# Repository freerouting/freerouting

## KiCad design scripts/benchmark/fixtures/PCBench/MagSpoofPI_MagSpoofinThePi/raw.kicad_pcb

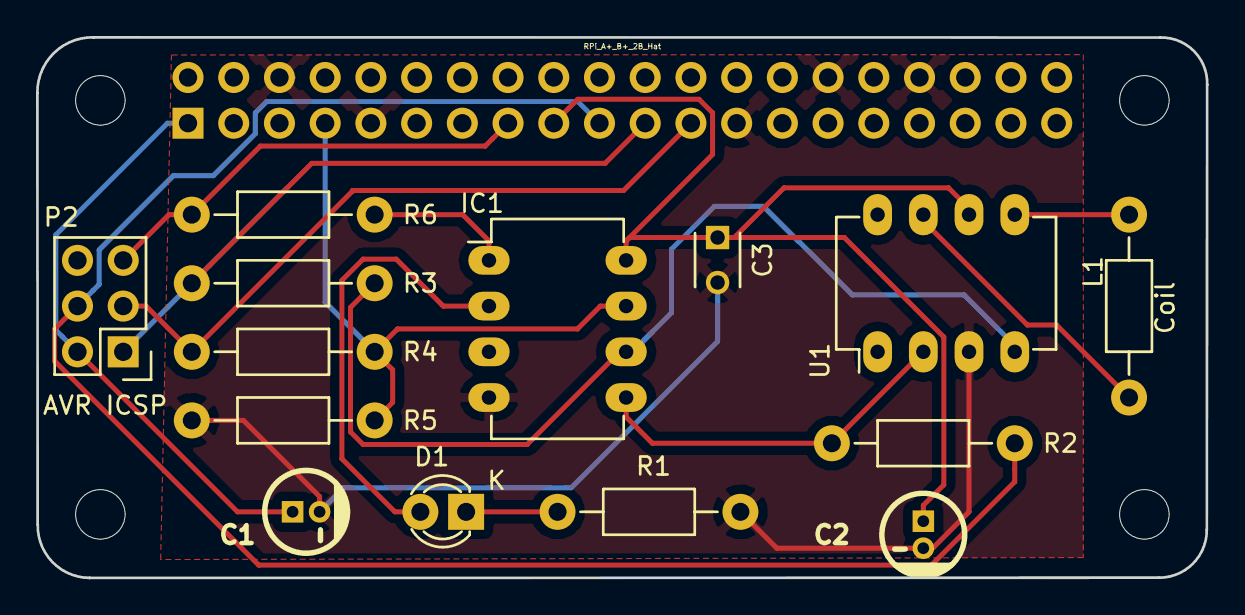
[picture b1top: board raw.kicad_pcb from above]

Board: 2 copper layers, 65.0 x 30.0 mm, 15 parts (0 on the bottom side), 14 nets.

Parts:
C1, C2: 100uF; CP_4x5mm
C3: 0.1uF; C_Disc_D3_P2.5
D1: LED; LED-3MM
IC1: ATTINY85-P; DIP-8_W7.62mm_LongPads
L1: Coil; Resistor_Horizontal_RM10mm
P2: AVR ICSP; Pin_Header_Straight_2x03
R1: 330; Resistor_Horizontal_RM10mm
R2, R3, R4, R6: 1K; Resistor_Horizontal_RM10mm
R5: 10K; Resistor_Horizontal_RM10mm
U1: TC4424; DIP-8_W7.62mm_LongPads
U2: RPi_A+_B+_2B_Hat; z_RPiZero_Hat_NPTH

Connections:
/GPIO4: IC1.7, R4.2, R5.1, U2.7
/MISO: P2.1, R3.1, U2.21
/MOSI: P2.4, R2.1, U2.19
/RST: P2.5, R6.2, U2.15
/SCK: P2.3, R4.1, U2.23
GND: C1.2, C2.2, C3.2, IC1.4, P2.6, R1.2, R5.2, U1.3, U2.6, U2.9, U2.25, U2.30, U2.34
unnamed: D1.1, R1.1
unnamed: D1.2, IC1.2
unnamed: IC1.1, R6.1
unnamed: IC1.5, R2.2, U1.2
unnamed: IC1.6, R3.2, U1.4
unnamed: L1.1, U1.7
unnamed: L1.2, U1.5
VCC: C1.1, C2.1, C3.1, IC1.8, P2.2, U1.6, U2.1, U2.17

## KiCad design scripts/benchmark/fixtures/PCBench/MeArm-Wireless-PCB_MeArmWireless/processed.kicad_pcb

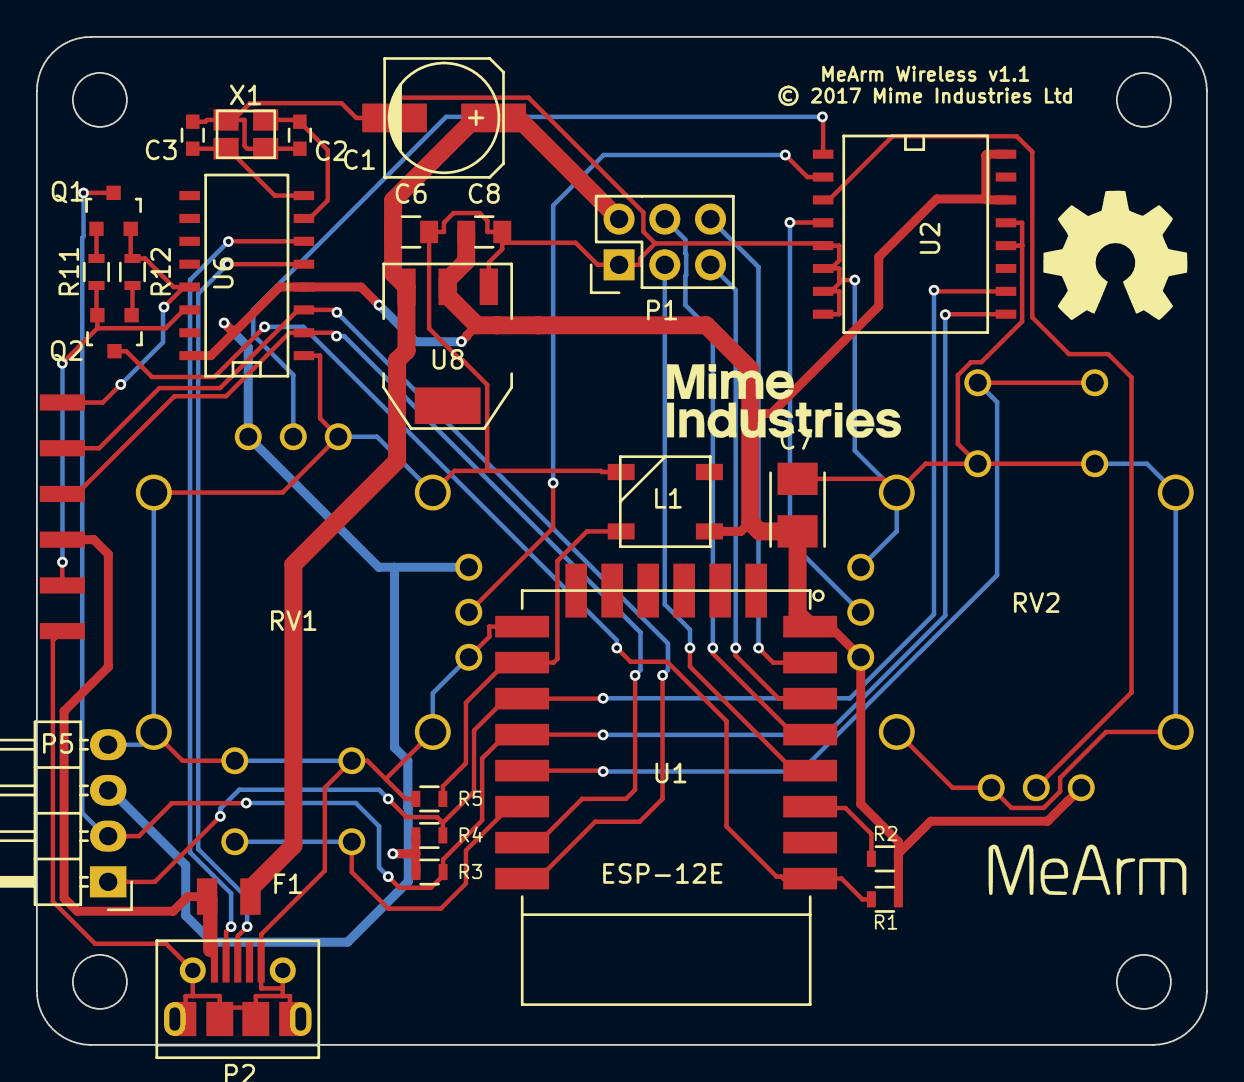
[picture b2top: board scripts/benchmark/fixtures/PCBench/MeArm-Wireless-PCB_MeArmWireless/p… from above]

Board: 2 copper layers, 65.0 x 56.0 mm, 31 parts (0 on the bottom side), 29 nets.

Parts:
ART1: OSHW-LOGO; OSHW_LOGO
ART2: LOGO; MEARM_LOGO_NEW
ART3: LOGO; MIME_LOGO
C1: 470uF; c_elec_6.3x7.7
C2, C3: 22pF; C_0603
C6, C8: 10uF; C_0805
C7: 100uF; TantalC_SizeB_EIA-3528_Reflow
F1: 1A; Fuse_SMD1206_Reflow
L1: WS2812B
P1: CONN_02X03; Pin_Header_Straight_2x03
P2: USB_OTG; MOLEX_MICRO_USB
P4: CONN_01X06; 6-PIN-EDGE-CONN
P5: CONN_01X04; Pin_Header_Angled_1x04
Q1, Q2: S8050; SOT-23
R1, R2, R3, R4, R5, R11, R12: 10k; R_0603
RV1, RV2: DUAL_POT_JOYSTICK; JOYSTICK
U1: ESP-12E
U2: PCF8591; SO-16-W
U6: CH340G; SO-16-N
U8: LD1117S33CTR; SOT-223
X1: 12MHz; crystal_FA238-TSX3225

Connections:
+3V3: C7.1, C8.1, L1.1, P5.3, R1.1, R2.1, R3.1, R4.1, RV1.1, RV1.4, RV2.1, RV2.4, U1.8, U2.14, U2.16, U6.4, U6.16, U8.2
+5V: F1.1, P2.1, P4.3
BASE_SERVO: P1.3, U1.4
BUTTON1: RV1.8, U1.20
BUTTON2: RV2.8, U1.19
GND: C1.2, C2.2, C3.2, C6.2, C7.2, C8.2, L1.3, P1.1, P2.5, P2.6, P4.1, P5.4, R5.2, RV1.3, RV1.6, RV1.7, RV1.9, RV2.3, RV2.6, RV2.7, RV2.9, U1.15, U2.5, U2.6, U2.7, U2.8, U2.12, U2.13, U6.1, U8.1, X1.3
GRIP_SERVO: P1.6, U1.7
LED: L1.4, R5.1, U1.16
LEFT_SERVO: P1.4, U1.5
unnamed: C2.1, U6.7, X1.1
unnamed: C3.1, U6.8, X1.2
unnamed: P2.2, U6.6
unnamed: P2.3, U6.5
unnamed: P4.2, Q2.1, R11.1, U6.14
unnamed: P4.6, Q1.1, R12.1, U6.13
unnamed: Q1.2, R11.2
unnamed: Q2.2, R12.2
unnamed: R2.2, U1.3
unnamed: RV1.2, U2.1
unnamed: RV1.5, U2.2
unnamed: RV2.2, U2.3
unnamed: RV2.5, U2.4
RESET: Q2.3, R1.2, U1.1
RIGHT_SERVO: P1.5, U1.6
RX: P4.4, U1.21, U6.2
SCL: P5.1, R4.2, U1.17, U2.10
SDA: P5.2, Q1.3, R3.2, U1.18, U2.9
TX: P4.5, U1.22, U6.3
VSS: C1.1, C6.1, F1.2, P1.2, U8.3

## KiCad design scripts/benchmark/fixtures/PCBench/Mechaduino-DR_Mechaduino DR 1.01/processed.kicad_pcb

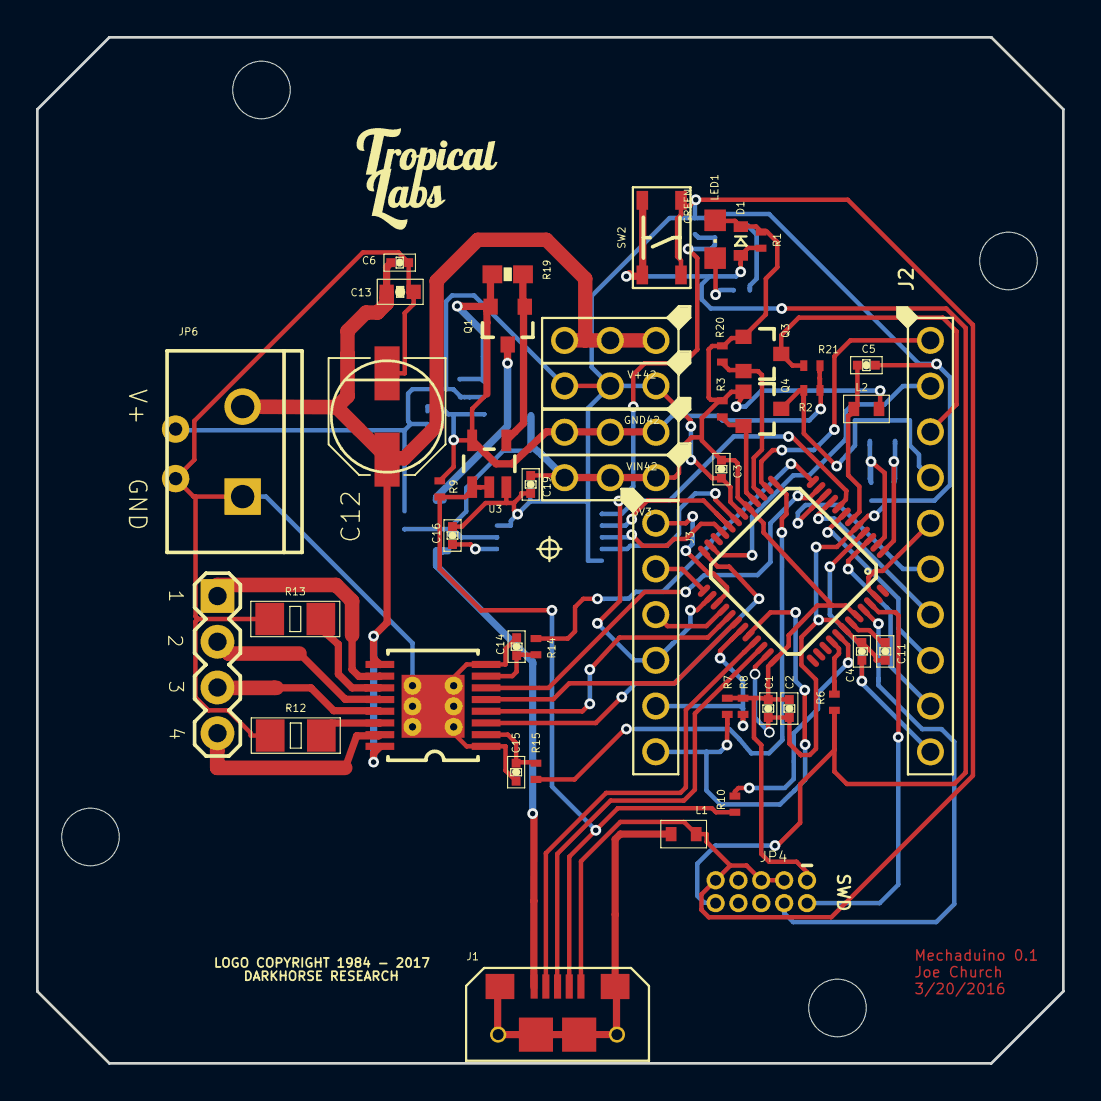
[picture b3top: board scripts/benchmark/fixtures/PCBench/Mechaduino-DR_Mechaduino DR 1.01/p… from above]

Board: 2 copper layers, 57.0 x 57.0 mm, 68 parts (0 on the bottom side), 60 nets.

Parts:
3V3: HEADER_01X03_2.54MM
C1, C2, C3, C4, C5, C9, C14, C15, C16, C19: 0.1uF; SWIFT_0402-CAP
C6: 0.01uF; 0402-CAP
C7, C8: 22pF; SWIFT_0402-CAP
C10: 10uF; 0805-CAP
C11, C17: 1uF; SWIFT_0402-CAP
C12: 100uF; CAPACITORS_ELECTROL_6.6X6.6
C13: 1.0uF; 0603-CAP
C18: 10.0uF; C0805
D1: DIODE_SOD-123
F1: 500mA; FUSE_SMD-PTC-1206
FRAME1: FRAME-LEDGER; CREATIVE_COMMONS
GND42: HEADER_01X03_2.54MM
HS: HS; Heat_Sink
IC1: SAMD21G18A-AUT; TQFP48-7X7
J1: USB_MICRO_RIGHT; USB_MICRO-RIGHT
J2: HEADER_01X10_2.54MM; PTH_2.54MM_01X10
J3: HEADER_01X06_2.54MM
JP4: SWD; CONNECTOR_PINHEAD-2X5-P127
JP6: CONNECTORS_M04PTH
L1: INDUCTOR_0603-TDK
L2: BLM18PG471SN1D; 0603-TDK
LED1: GREEN; CHIPLED_0805
MOTOR_POWER42: SCREWTERMINAL-5MM-2
MOT_GRAPHICS_1: WANTAI_57BYGH115-003B; MOT_GRAPHICS_1
Q1: 2.5A 30V; MOSFET_P_CHANNEL_SOT23
Q2: 2N7002PW; DISCRETE_SEMI_SOT323
Q3, Q4: BSS138; MOSFET-N_CHANNEL_SOT23-3
R1, R9, R16: 100K; R0402
R2, R3, R20, R21: 10K; R0402
R5, R6, R10: 330; R0402
R7, R8: 4.7K; R0402
R12, R13: 0.15 ohm; R1206
R14, R15: 1K; R0402
R19: 47K; 0603-RES
SH1: SHORT-HA5; SHORT_ALL-50
SW2: TACT_4.2MM
U1: AS5047D_TSSOP14
U2: ALLEGRO_A4954_TSSOP16
U3: 74AHC1G125; DIGITAL_IC_SOT23-5
U4: 3.3V_REG; SOT23-5_1
U$3: TROPICAL_LABS_LOGO_1LOGO3; LOGO3
U$5: MECHADUINO_LOGO
V+42: HEADER_01X03_2.54MM
VIN42: HEADER_01X03_2.54MM
Y1: 32,768Khz; CRYSTAL-SMD-2.0X1.2

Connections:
3.3V: 3V3.P$1, 3V3.P$2, 3V3.P$3, C1.1, C2.1, C3.1, C10.1, C17.1, C19.1, D1.K, IC1.17, IC1.36, IC1.44, JP4.1, L2.1, LED1.A, Q3.1, Q4.1, R1.1, R3.1, R7.1, R8.1, R20.1, U1.12, U4.5
/ARDUINO_A0: IC1.3, J2.P$9
/ARDUINO_A1: IC1.7, J2.P$8
/ARDUINO_A2----HEADER_SS: IC1.8, U1.1
/ARDUINO_A3: IC1.9, J2.P$7
/ARDUINO_A4: IC1.10, J2.P$6
/ARDUINO_A5: IC1.47, J2.P$5
/ARDUINO_AREF: C4.1, IC1.4, J2.P$10
/ARDUINO_D0: IC1.16, Q4.2, R3.2
/ARDUINO_D1: IC1.15, Q3.2, R20.2
/ARDUINO_D2: IC1.23, J2.P$2
/ARDUINO_D3: IC1.14, J2.P$1
/ARDUINO_D4----VREF2: IC1.13, R15.2
/ARDUINO_D5----IN3: IC1.24, U2.3
/ARDUINO_D6----IN4: IC1.29, U2.4
/ARDUINO_D7----IN2: IC1.30, U2.5
/ARDUINO_D8----IN1: IC1.11, U2.6
/ARDUINO_D9----VREF1: IC1.12, R14.2
/ARDUINO_D10_SS: IC1.27, J3.P$1
/ARDUINO_D11_MOSI: IC1.25, J3.P$2
/ARDUINO_D12_MISO: IC1.28, J3.P$3
/ARDUINO_D13_SCK: IC1.26, J3.P$4, Q2.1, R16.1
/ARDUINO_D20_SDA: IC1.31, J3.P$5, R8.2
/ARDUINO_D21_SCL: IC1.32, J3.P$6, R7.2
/HEADER_MISO: IC1.21, U1.3
/HEADER_MOSI: IC1.19, U1.4
/HEADER_SCK: IC1.20, U1.2
/HV1: J2.P$3, Q3.3, R21.2
/HV2: J2.P$4, Q4.3, R2.2
/N$1: LED1.C, R5.1
/N$2: R12.2, U2.14
/N$3: Q2.3, R5.2
/N$4: R13.2, U2.11
/N$6: C15.1, R15.1, U2.2
/N$7: J1.4, R9.2, R10.1, U3.1, U3.2
/N$13: JP6.4, U2.15
/N$14: JP6.1, U2.10
/N$15: JP6.2, U2.12
/N$16: JP6.3, U2.13
/N$27: C16.1, U1.11
/N$32: C14.1, R14.1, U2.7
/N$33: F1.2, Q1.3
/N$34: Q1.1, R19.2, U3.4
/N$36: F1.1, J1.1
/PA00_XIN32: C7.2, IC1.1, Y1.2
/PA01_XOUT32: C8.2, IC1.2, Y1.1
/PA28_USB_HOST_EN: IC1.41, R10.2
/PA30_SWCLK: IC1.45, JP4.4
/PA31_SWDIO: IC1.46, JP4.2
/RESET: D1.A, JP4.10, R1.2, R6.1, SW2.P$1, SW2.P$2
/TARGET_RESET_EDBG: IC1.40, R6.2
/TARGET_USB_N: IC1.33, J1.2
/TARGET_USB_P: IC1.34, J1.3
/VDDANA: C5.1, IC1.6, L2.2
/VDDCORE: C11.1, IC1.43
GND: C1.2, C2.2, C3.2, C4.2, C5.2, C7.1, C8.1, C9.2, C10.2, C11.2, C16.2, C17.2, C18.2, C19.2, GND42.P$1, GND42.P$2, GND42.P$3, IC1.5, IC1.18, IC1.35, IC1.42, J1.5, JP4.3, JP4.5, JP4.9, L1.2, Q2.2, R16.2, SH1.2, SW2.P$3, SW2.P$4, U1.5, U1.13, U3.3, U4.2
GND2: C6.2, C12.-, C13.2, C14.2, C15.2, HS.HS, HS.~, MOTOR_POWER42.1, R12.1, R13.1, SH1.1, U2.1, U2.8
SLD: J1.S1, J1.S2, J1.S3, J1.S4, J1.S5, J1.S6, L1.1
V+: C6.1, C12.+, C13.1, MOTOR_POWER42.2, U2.9, U2.16, V+42.P$1, V+42.P$2, V+42.P$3
VIN: C9.1, C18.1, Q1.2, R2.1, R9.1, R19.1, R21.1, U3.5, U4.1, U4.3, VIN42.P$1, VIN42.P$2, VIN42.P$3

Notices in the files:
scripts/benchmark/fixtures/PCBench/MeArm-Wireless-PCB_MeArmWireless/processed.kicad_pcb:
© 2017 Mime Industries Ltd
parts and their libraries:
Released under the Creative Commons Attribution Share-Alike 4.0 License
https://creativecommons.org/licenses/by-sa/4.0
